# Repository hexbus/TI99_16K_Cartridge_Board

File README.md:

# TI-99/4A 16K Cartridge Board

## PCB ordering

- **[Download the Gerbers — v2a with VPP supply correction, 9 November 2026](https://github.com/hexbus/TI99_16K_Cartridge_Board/raw/refs/heads/main/gerbers/TI99-16K-v2a-VPP-gerbers-20261109.zip)**
- **[Open JLCPCB using my referral link](https://jlcpcb.com/?from=RVDYTTLKZHK)**

Download the Gerber ZIP, open JLCPCB through the referral link, and upload the ZIP directly. It contains both copper layers, both solder-mask layers, top silkscreen, the board outline and plated NC drills. No stencil or assembly files are included.

Confirm **2 copper layers** and an overall outline of **100.0252 × 64.008 mm**, including the connector tongue. The width is slightly greater than 100 mm; do not scale the files to meet a pricing tier. Confirm board thickness, connector contact finish and any bevel requirements for your cartridge socket before ordering; these manufacturing options are not specified in the original source archive.

The referral link does not upload files automatically. I may receive referral rewards for qualifying new users.

## Current fabrication revision

The ExpressPCB v2a artwork was converted to [an editable KiCad 10 PCB](hardware/TI99-16K-v2a-converted.kicad_pcb), with its [project settings](hardware/TI99-16K-v2a-converted.kicad_pro). The [original ExpressPCB archive](16k_cart.zip) remains unchanged for reference.

**The sole electrical change is a 0.254 mm top-layer trace connecting U1 pin 1 (VPP) to pin 28 (+5 V).** The original left pin 1 unconnected. Intel's [M27C128 datasheet](https://deramp.com/downloads/mfe_archive/050-Component%20Specifications/Intel/Memory%20Components/Intel%20M27C128.pdf), read-operation table on page 7-43, permits VPP connected directly to VCC. Program the EPROM separately; this is a read-only cartridge, not an in-circuit programmer. Check the requirements of the actual EPROM you fit.

Original copper, pad positions, outline and hole locations are otherwise preserved. The converted silkscreen uses a different stroke font, retains the original credits, and adds `VPP +5V REV 2026`. The resistor value text was sized to fit its outline. Both original connector mask openings are retained; through-hole pad mask openings extend 0.05 mm beyond the copper.

| Top | Bottom, viewed from underneath |
| --- | --- |
|  |  |

These previews are rendered from the delivered ZIP; colors do not specify a surface finish.

The original IC footprints have 2.54 mm pin pitch: U1 uses 15.24 mm rows and U2 uses 7.62 mm rows, consistent with the [TI 27C128 DIP specification](https://deramp.com/downloads/mfe_archive/050-Component%20Specifications/Texas%20Instruments/Memory%20Components/TI%20TMS27C128.pdf) and [TI 16-pin PDIP drawing](https://www.ti.com/lit/ml/mpdi002c/mpdi002c.pdf). Both notches face left in the top preview; the square pad marks pin 1.

The exact ZIP was checked against the decoded original geometry plus the VPP trace, including copper, outline, all 73 plated drill positions/sizes, mask openings on all through-hole pads, and all 18 connector fingers per side. The added trace clears unrelated copper. Pin-1 orientation and IC supply pins were checked against the Intel and [TI LS379 datasheets](https://www.ti.com/lit/ds/symlink/sn54ls377.pdf). There is no reconstructed schematic/ERC check. DRC retains warnings for intentional shared finger mask openings, open finger ends and the original mounting-circle silk clipped from the export.

**This conversion and VPP revision have not been fabricated or tested.** Cartridge connector mapping/mechanical fit, board thickness, socket and component lead fit, soldering, bank-switch timing and operation still require hardware verification. The ZIP includes checksums, the license and the original README.

## Background
This is the original 16K EPROM Cartridge board for TI-99/4A from www.hexbus.com.  I designed it back in 2009-2010.

## Original README
This 16K .pcb file was made with ExpressPCB (www.expresspcb.com).

You can use and make changes to this file as long as the copyright notices
remain intact on the board and this file is distributed with it.  

This file is (c) 2009 www.hexbus.com, (c) 2007 www.ti-994a.com. Thanks to 
www.mainbyte.com for the idea to make this.

If you make any changes and would like to share them with me, I would love to
see this board continue to improve and become something more....

Jon Guidry

www.hexbus.com

acadiel%guidry.org (replace % with @)

## Usage
See attached license

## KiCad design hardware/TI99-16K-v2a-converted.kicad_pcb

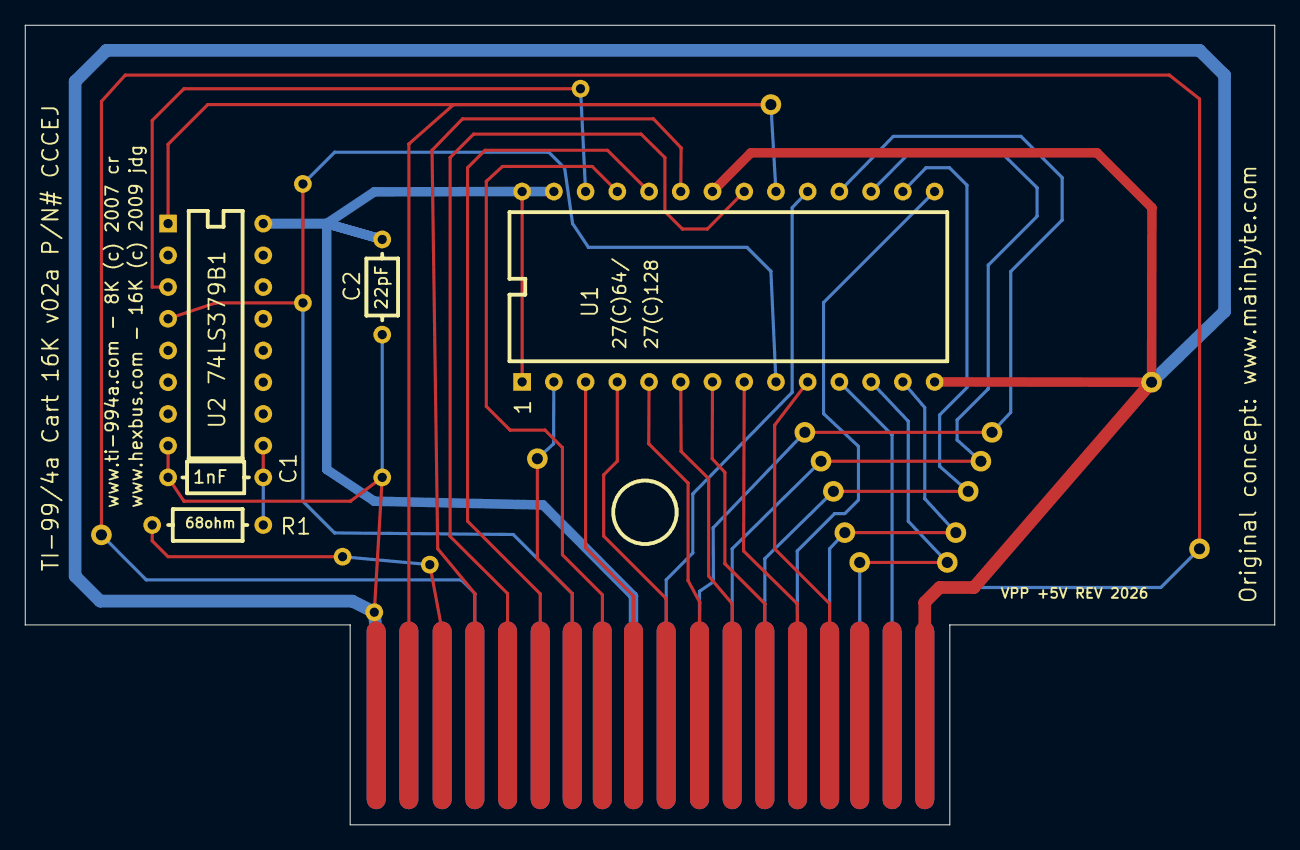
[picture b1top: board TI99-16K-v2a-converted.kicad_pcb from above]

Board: 2 copper layers, 100.0 x 64.0 mm, 6 parts (0 on the bottom side), 14 nets.

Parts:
C1, C2: Original ExpressPCB geometry
J0: Original ExpressPCB geometry
R1: Original ExpressPCB geometry
U1, U2: Original ExpressPCB geometry

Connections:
N36: J0.S194, U1.2
N107: C2.1, U1.1, U1.27, U1.28, U2.16
N109: J0.S324, J0.S348, U1.17
N110: J0.S278, J0.S351, U1.12
N111: J0.S327, J0.S349, U1.16
N113: J0.S330, J0.S350, U1.13
N116: J0.S117, J0.S120
N154: J0.S459, J0.S497, U1.9, U2.4
N163: J0.S281, J0.S347, U1.18
N165: J0.S183, U1.20, U2.1
N171: J0.S427, U1.26, U2.3
N196: C1.2, C2.2, J0.S134, J0.S356, J0.S460, U1.14, U1.22, U2.8
N444: J0.S444, J0.S466, R1.2
N464: C1.1, R1.1, U2.9

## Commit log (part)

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2025-04-10 Delete LICENSE
    changing licenses to MIT
2025-04-10 Create LICENSE

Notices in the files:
hardware/TI99-16K-v2a-converted.kicad_pcb:
www.ti-994a.com - 8K (c) 2007 cr
www.hexbus.com - 16K (c) 2009 jdg
